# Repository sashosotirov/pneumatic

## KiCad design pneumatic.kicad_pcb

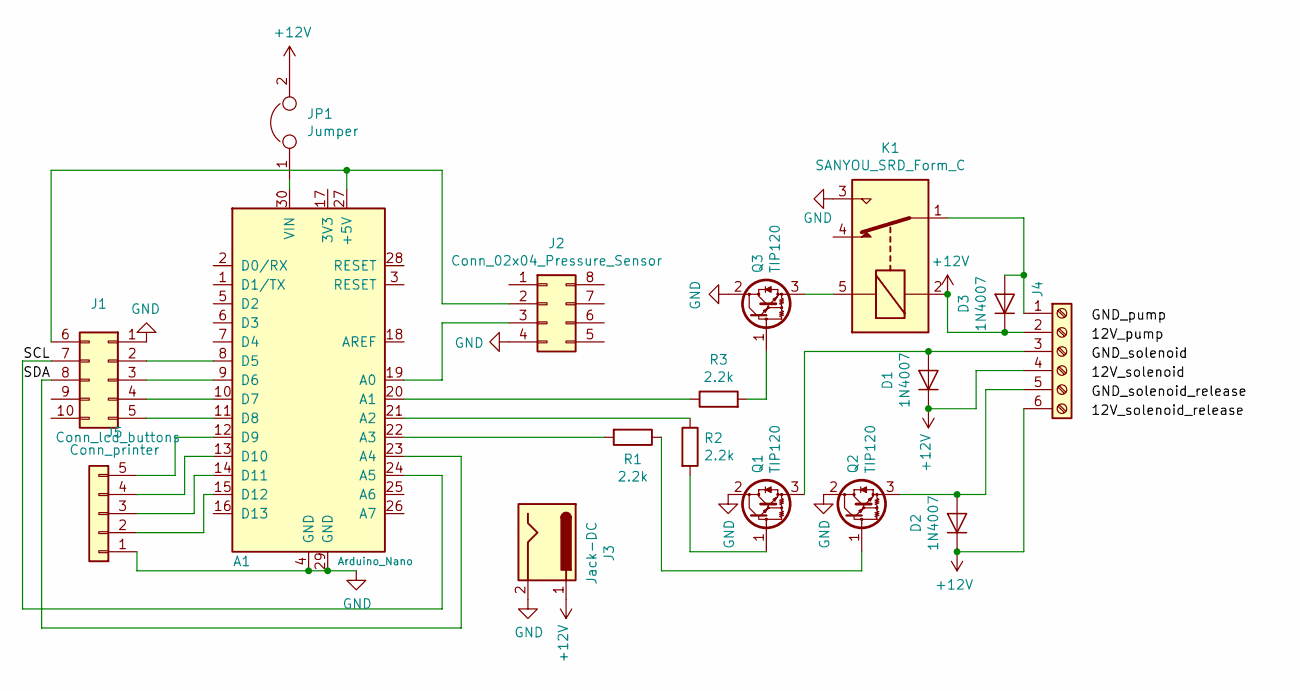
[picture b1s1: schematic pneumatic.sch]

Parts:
A1: Arduino_Nano; Arduino_Nano_WithMountingHoles
D1, D2, D3: 1N4007; D_DO-41_SOD81_P7.62mm_Horizontal
J1: Conn_lcd_buttons; IDC-Header_2x05_P2.54mm_Vertical
J2: Conn_02x04_Pressure_Sensor; pressure_sensor
J3: Jack-DC; BarrelJack_Horizontal
J4: Screw_Terminal_01x06; TerminalBlock_4Ucon_1x06_P3.50mm_Horizontal
J5: Conn_printer; PinHeader_1x05_P2.54mm_Vertical
JP1: Jumper; SolderJumper-2_P1.3mm_Bridged2Bar_Pad1.0x1.5mm
K1: SANYOU_SRD_Form_C; Relay_SUN_HOLD_RAS_series
Q1, Q2, Q3: TIP120; TO-220-3_Vertical
R1, R2, R3: 2.2k; R_Axial_DIN0207_L6.3mm_D2.5mm_P7.62mm_Horizontal

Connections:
+12V: D1.1 (K), D2.1 (K), D3.1 (K), J3.1, J4.2, J4.4, J4.6, JP1.2, K1.2
/SCL: A1.24 (A5), J1.7
GND: A1.4 (GND), A1.29 (GND), J1.1, J2.4, J3.2, J5.1, K1.3, Q1.2 (C), Q2.2 (C), Q3.2 (C)
unnamed: A1.8 (D5), J1.2
unnamed: A1.9 (D6), J1.3
unnamed: A1.10 (D7), J1.4
unnamed: A1.11 (D8), J1.5
unnamed: A1.12 (D9), J5.5
unnamed: A1.13 (D10), J5.4
unnamed: A1.14 (D11), J5.3
unnamed: A1.15 (D12), J5.2
unnamed: A1.19 (A0), J2.3
unnamed: A1.20 (A1), R3.1
unnamed: A1.21 (A2), R2.1
unnamed: A1.22 (A3), R1.2
unnamed: A1.23 (A4), J1.8
unnamed: A1.27 (+5V), J1.6, J2.2
unnamed: A1.30 (VIN), JP1.1
unnamed: D1.2 (A), J4.3, Q1.3 (E)
unnamed: D2.2 (A), J4.5, Q2.3 (E)
unnamed: D3.2 (A), J4.1, K1.1
unnamed: K1.5, Q3.3 (E)
unnamed: Q1.1 (B), R2.2
unnamed: Q2.1 (B), R1.1
unnamed: Q3.1 (B), R3.2

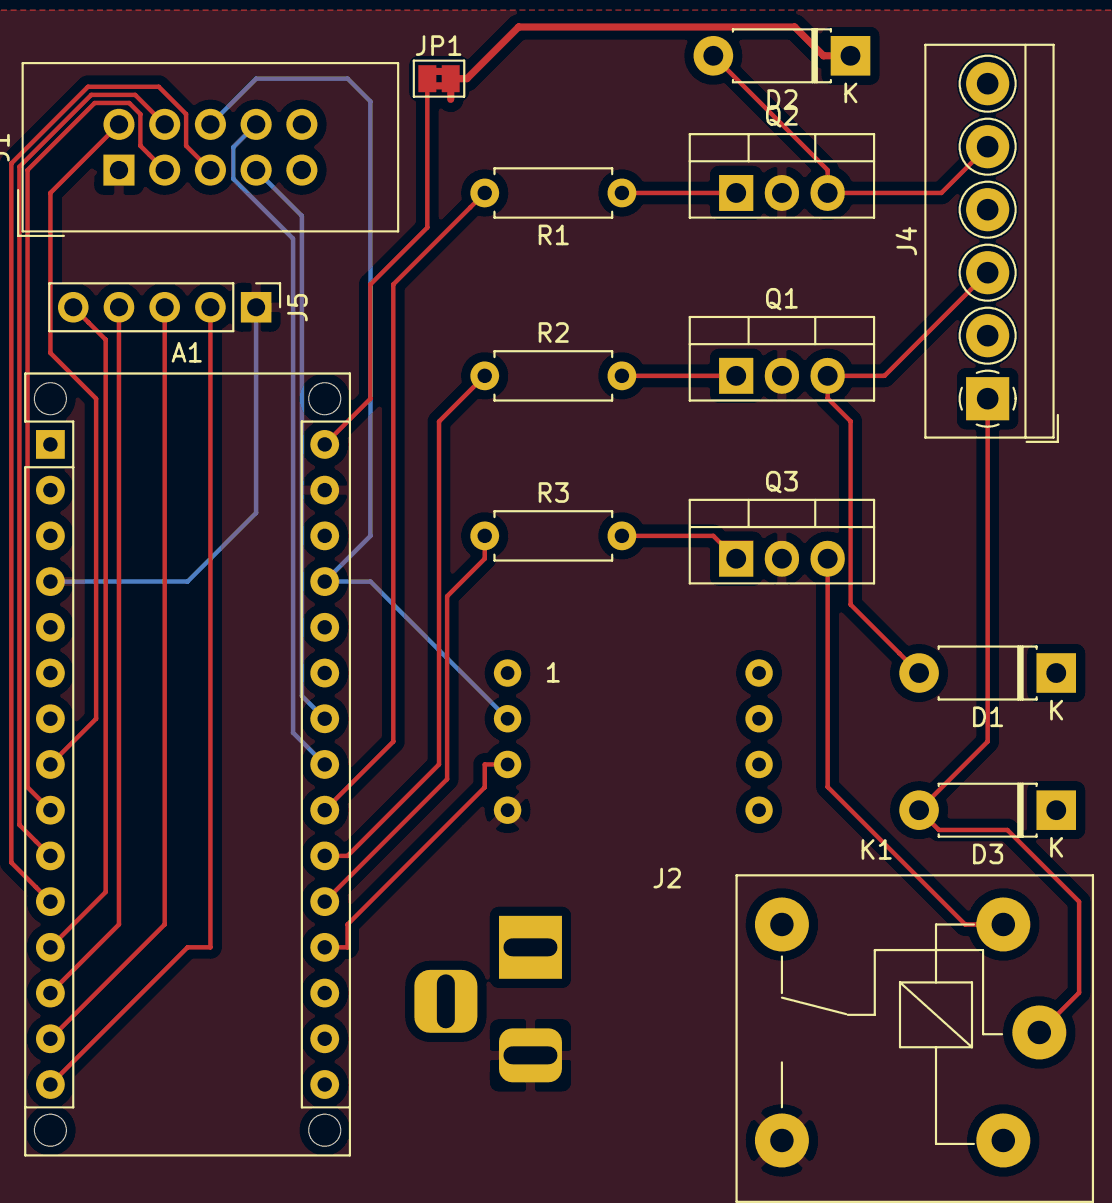
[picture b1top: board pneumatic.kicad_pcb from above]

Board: 2 copper layers, 17 parts (1 on the bottom side), 25 nets.

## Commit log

2019-08-23 pneumatic board with printer connection
